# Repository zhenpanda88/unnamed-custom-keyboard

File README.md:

# untitled-keyboard-project
Unnamed custom mechanical keyboard project. I might finish this one day. It'll probably be a split layout. But eh...

Project Roadmap:
- V.0: Simple layout prototype for minimal functionality and software testing (probably 40%-size amount of keys)
- V.1: Ergonomic form layout and bigger layout (60%+ or 40% with different layers)
- V.2+: Bluetooth support, different layouts, on board LED display, backlighting (stretch goal, I doubt I will get this far lol)

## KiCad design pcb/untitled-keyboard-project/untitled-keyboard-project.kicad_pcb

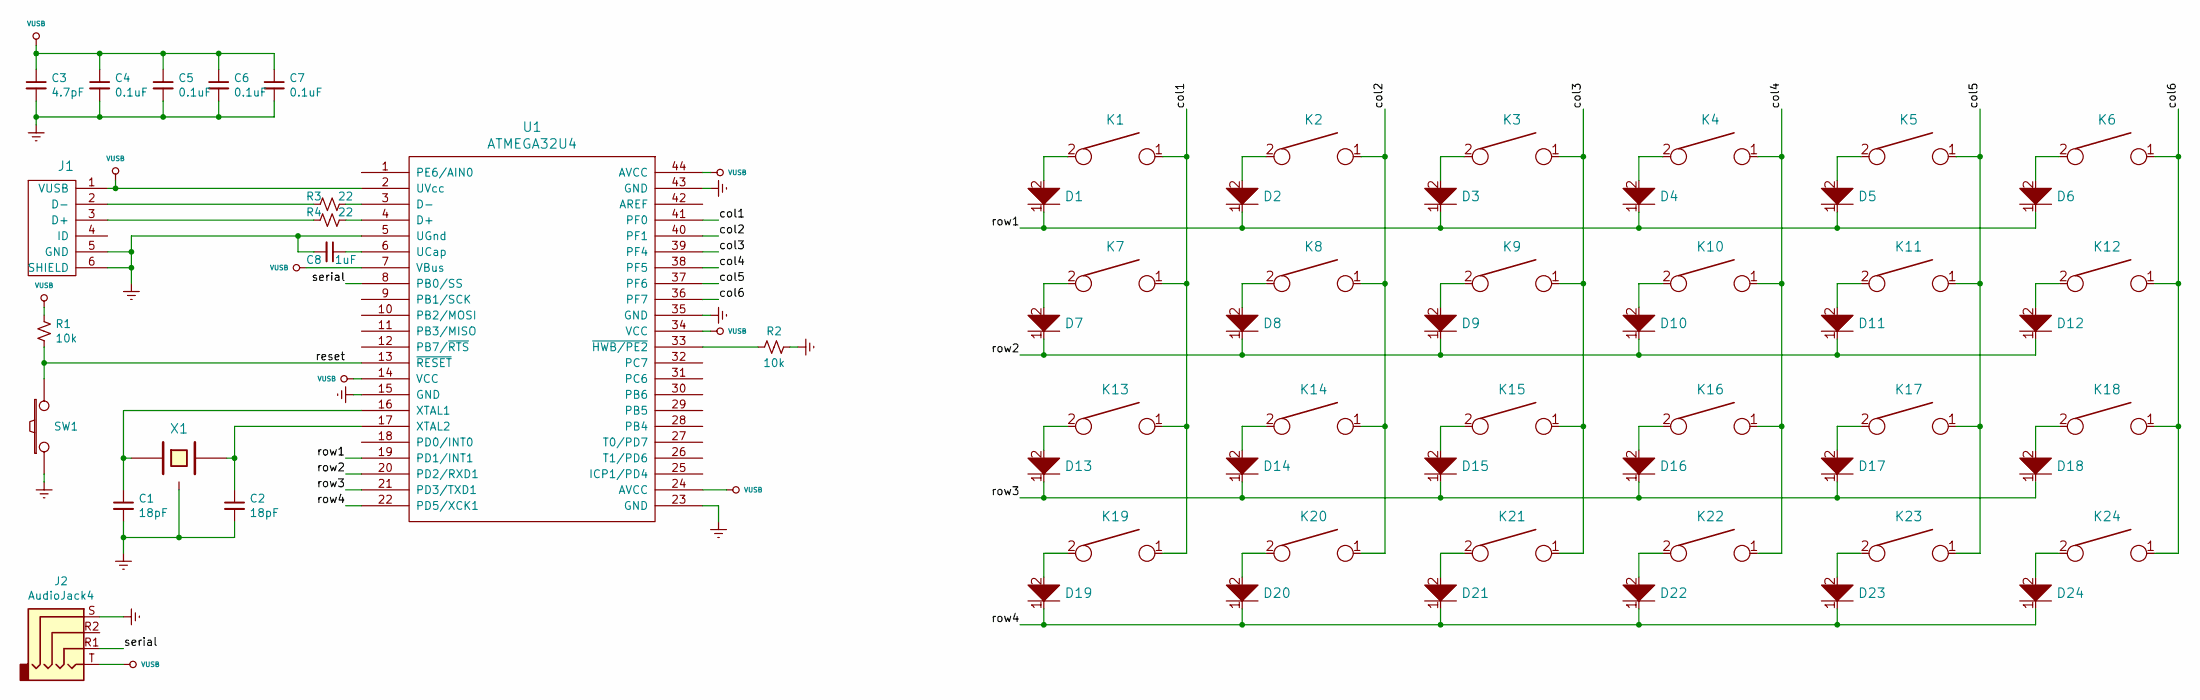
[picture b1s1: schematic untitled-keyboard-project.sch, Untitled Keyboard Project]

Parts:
C1, C2: 18pF; C_0805_2012Metric
C3: 4.7pF; C_0805_2012Metric
C4, C5, C6, C7: 0.1uF; C_0805_2012Metric
C8: 1uF; C_0805_2012Metric
D1, D2, D3, D4, D5, D6, D7, D8, D9, D10, D11, D12, D13, D14, D15, D16, D17, D18, D19, D20, D21, D22, D23, D24: D; D_0603_1608Metric
J1: USB_mini_micro_B; USB_Micro-B_Molex-105017-0001
J2: AudioJack4; Jack_3.5mm_PJ320E_Horizontal
K1, K2, K3, K4, K5, K6, K7, K8, K9, K10, K11, K12, K13, K14, K15, K16, K17, K18, K19, K20, K21, K22, K23, K24: KEYSW; SW_Cherry_MX_1.00u_PCB
R1, R2: 10k; R_0805_2012Metric
R3, R4: 22; R_0805_2012Metric
SW1: SW_PUSH; SW_SPST_TL3342
U1: ATMEGA32U4; TQFP-44_10x10mm_P0.8mm
X1: XTAL_GND; Crystal_SMD_TXC_7M-4Pin_3.2x2.5mm

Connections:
/col1: K1.1, K7.1, K13.1, K19.1, U1.41 (PF0)
/col2: K2.1, K8.1, K14.1, K20.1, U1.40 (PF1)
/col3: K3.1, K9.1, K15.1, K21.1, U1.39 (PF4)
/col4: K4.1, K10.1, K16.1, K22.1, U1.38 (PF5)
/col5: K5.1, K11.1, K17.1, K23.1, U1.37 (PF6)
/col6: K6.1, K12.1, K18.1, K24.1, U1.36 (PF7)
/reset: R1.1, SW1.2, U1.13 (~RESET)
/row1: D1.1, D2.1, D3.1, D4.1, D5.1, D6.1, U1.19 (PD1/INT1)
/row2: D7.1, D8.1, D9.1, D10.1, D11.1, D12.1, U1.20 (PD2/RXD1)
/row3: D13.1, D14.1, D15.1, D16.1, D17.1, D18.1, U1.21 (PD3/TXD1)
/row4: D19.1, D20.1, D21.1, D22.1, D23.1, D24.1, U1.22 (PD5/XCK1)
/serial: J2.R1, U1.8 (PB0/SS)
GNDREF: C1.2, C2.2, C3.2, C4.2, C5.2, C6.2, C7.2, C8.2, J1.5 (GND), J1.6 (SHIELD), J2.S, R2.2, SW1.1, U1.5 (UGnd), U1.15 (GND), U1.23 (GND), U1.35 (GND), U1.43 (GND), X1.2, X1.4
unnamed: C1.1, U1.16 (XTAL1), X1.1
unnamed: C2.1, U1.17 (XTAL2), X1.3
unnamed: C8.1, U1.6 (UCap)
unnamed: D1.2, K1.2
unnamed: D2.2, K2.2
unnamed: D3.2, K3.2
unnamed: D4.2, K4.2
unnamed: D5.2, K5.2
unnamed: D6.2, K6.2
unnamed: D7.2, K7.2
unnamed: D8.2, K8.2
unnamed: D9.2, K9.2
unnamed: D10.2, K10.2
unnamed: D11.2, K11.2
unnamed: D12.2, K12.2
unnamed: D13.2, K13.2
unnamed: D14.2, K14.2
unnamed: D15.2, K15.2
unnamed: D16.2, K16.2
unnamed: D17.2, K17.2
unnamed: D18.2, K18.2
unnamed: D19.2, K19.2
unnamed: D20.2, K20.2
unnamed: D21.2, K21.2
unnamed: D22.2, K22.2
unnamed: D23.2, K23.2
unnamed: D24.2, K24.2
unnamed: J1.2 (D-), R3.1
unnamed: J1.3 (D+), R4.1
unnamed: R2.1, U1.33 (~HWB/PE2)
unnamed: R3.2, U1.3 (D-)
unnamed: R4.2, U1.4 (D+)
VUSB: C3.1, C4.1, C5.1, C6.1, C7.1, J1.1 (VUSB), J2.T, R1.2, U1.2 (UVcc), U1.7 (VBus), U1.14 (VCC), U1.24 (AVCC), U1.34 (VCC), U1.44 (AVCC)

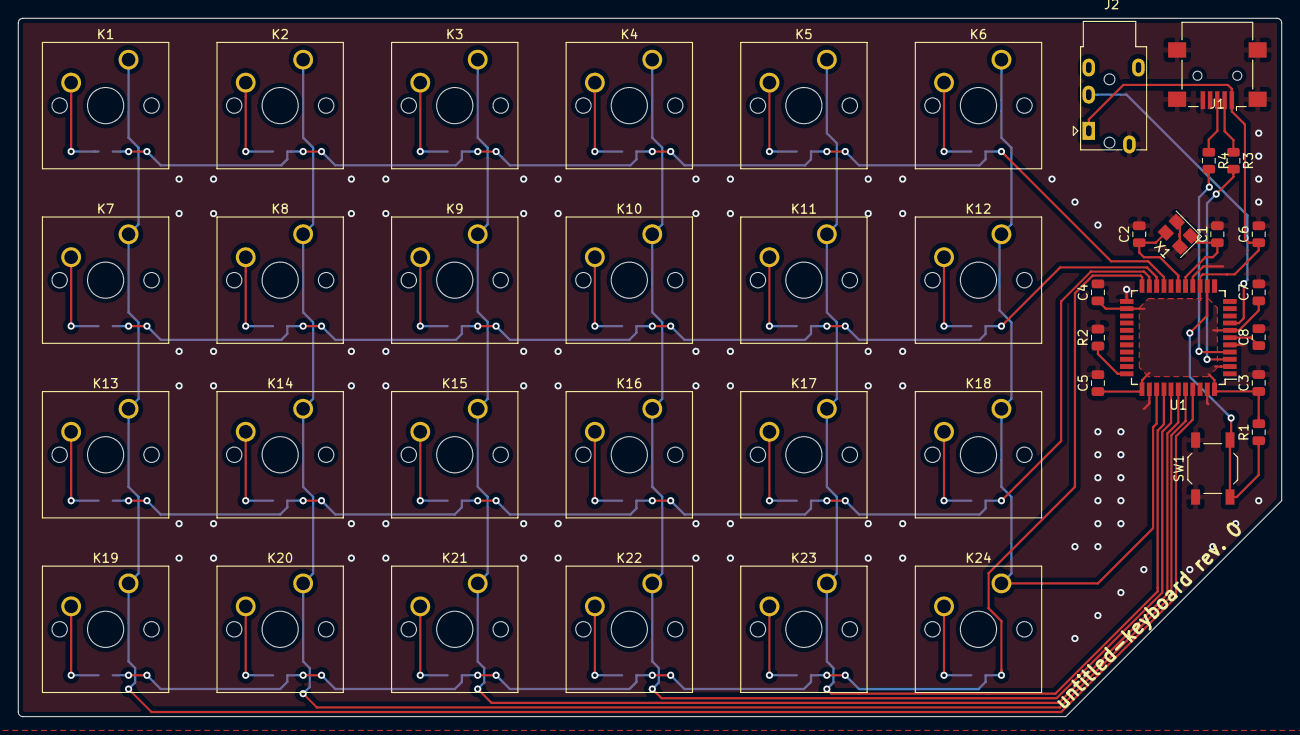
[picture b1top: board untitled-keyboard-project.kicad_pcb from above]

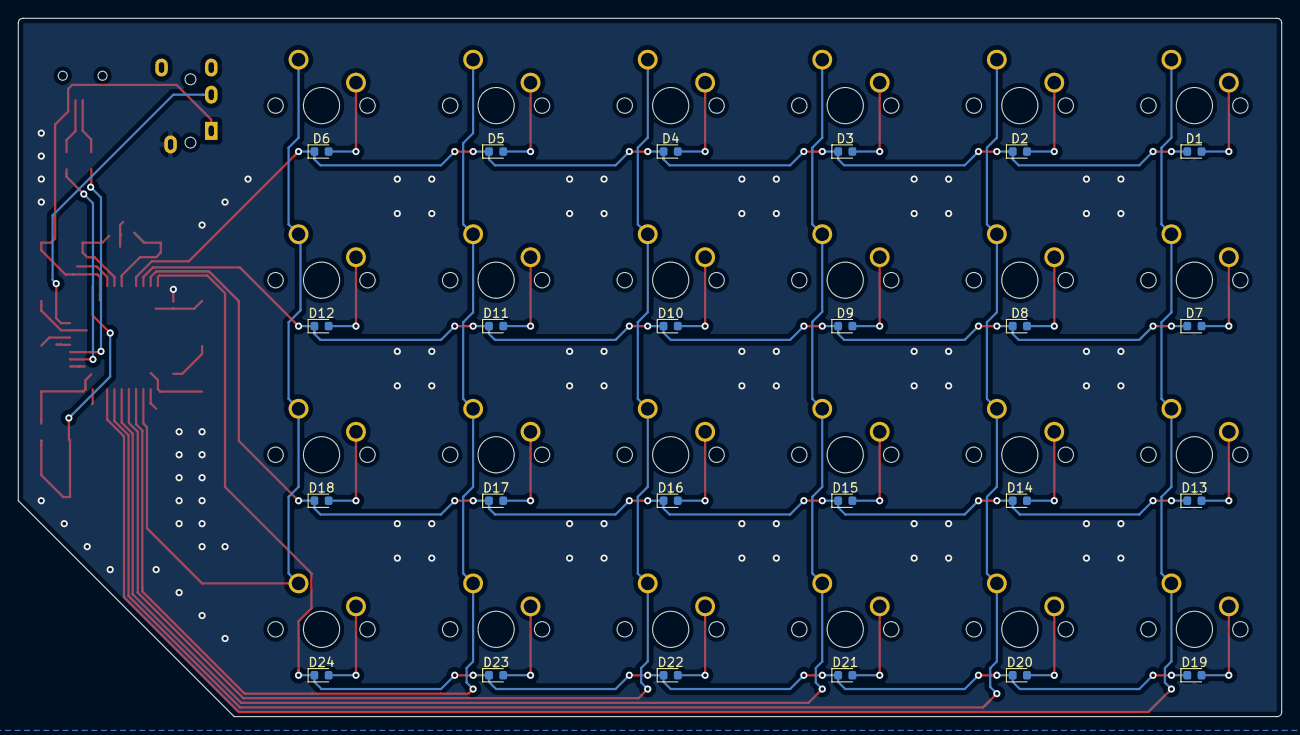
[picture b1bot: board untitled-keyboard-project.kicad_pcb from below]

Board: 2 copper layers, 139.7 x 77.2 mm, 65 parts (24 on the bottom side), 46 nets.

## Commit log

2019-12-12 Created KiCAD Project
    Created KiCAD project workspace (schematic and pcb).
2019-12-12 Update 12/11/19 23:46
    Added microprocessor and peripherals to schematic. Added empty BOM excel sheet.
2019-12-12 Update 12/12/19 00:23
    Renamed KiCAD project to "Untitled Keyboard Project" and created a left and a right side schematic.
2019-12-12 Update 12/12/19 13:58
    Updated README and BOM
2019-12-15 Added switches to right side PCB schematic
2019-12-18 Update 12/18/19 00:36
    Fixed net labels and assigned footprints to schematic symbols.
2019-12-23 Update 12/23/19 00:05
    Reorganized KiCAD project. Created PCB file and started laying out components.
2020-01-02 Finished layout for Rev 0 board
2020-01-02 Updated Gerbers
2020-11-29 Update 11/28/2020
    Capacitor Value Change
    File Cleanup
